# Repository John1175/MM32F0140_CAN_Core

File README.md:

# MM32F0140_CAN_Core
带CAN的MM32F0140核心板

KiCad绘制

CAN接口

SWD接口

USB串口

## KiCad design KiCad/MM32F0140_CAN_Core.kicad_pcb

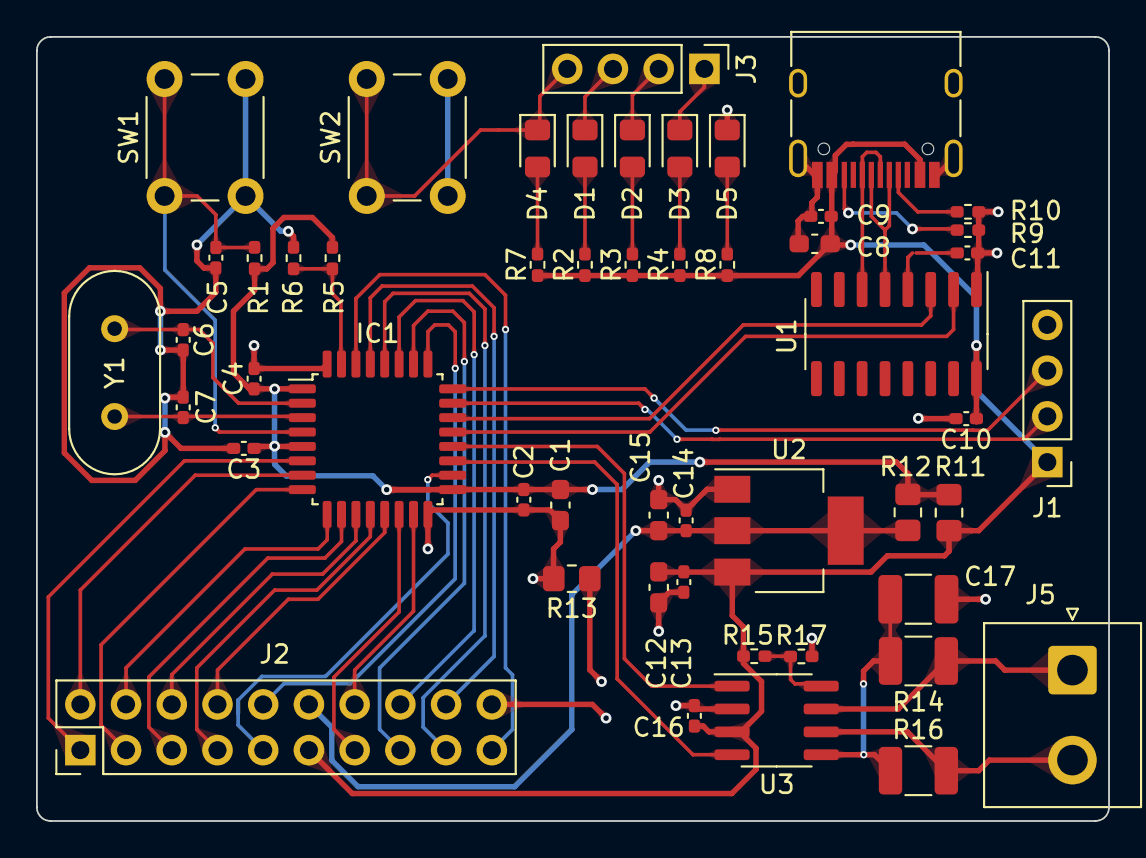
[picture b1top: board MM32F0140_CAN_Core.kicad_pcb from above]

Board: 2 copper layers, 59.6 x 43.6 mm, 51 parts (0 on the bottom side), 50 nets.

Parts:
C1, C8, C12, C15: 10uF; C_0603_1608Metric_Pad1.08x0.95mm_HandSolder
C2, C3, C4, C5, C9, C11, C13, C14, C16: 0.1uF; C_0402_1005Metric_Pad0.74x0.62mm_HandSolder
C6, C7: 22pF; C_0402_1005Metric_Pad0.74x0.62mm_HandSolder
C10: 0.47uF; C_0402_1005Metric_Pad0.74x0.62mm_HandSolder
C17: 4.7nF; C_1210_3225Metric_Pad1.33x2.70mm_HandSolder
D1, D2, D3, D4, D5: LED; LED_0805_2012Metric_Pad1.15x1.40mm_HandSolder
IC1: MM32F0144C4P; LQFP-32_7x7mm_P0.8mm
J1, J3: Conn_01x04; PinHeader_1x04_P2.54mm_Vertical
J2: Conn_02x10_Top_Bottom; PinHeader_2x10_P2.54mm_Vertical
J4: USB_C_Receptacle_USB2.0; USB_C_Receptacle_HRO_TYPE-C-31-M-12
J5: Conn_01x02; JST_NV_B02P-NV_1x02_P5.00mm_Vertical
R1: 100K; R_0402_1005Metric_Pad0.72x0.64mm_HandSolder
R2, R3, R4, R5, R6, R7, R8, R15, R17: 10K; R_0402_1005Metric_Pad0.72x0.64mm_HandSolder
R9, R10: 5.1K; R_0402_1005Metric_Pad0.72x0.64mm_HandSolder
R11, R12, R13: 0R; R_0805_2012Metric_Pad1.20x1.40mm_HandSolder
R14, R16: 60R; R_1210_3225Metric_Pad1.30x2.65mm_HandSolder
SW1, SW2: SW_Push; SW_PUSH_6mm_H5mm
U1: CH340C; SOIC-16_3.9x9.9mm_P1.27mm
U2: AMS1117; SOT-223-3_TabPin2
U3: TJA1040T; SOIC-8_3.9x4.9mm_P1.27mm
Y1: 8MHz; Crystal_HC49-U_Vertical

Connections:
+5V: C8.1, C9.1, C10.1, C12.1, C13.1, C16.1, J1.1, J2.11, J4.A4 (VBUS), J4.A9 (VBUS), J4.B4 (VBUS), J4.B9 (VBUS), R2.1, R3.1, R4.1, R7.1, R8.1, R11.1, R15.1, U1.16 (VCC), U2.3 (VI), U3.3 (VCC)
/CAN/CAN_RX: IC1.19 (PA9), U3.4 (RXD)
/CAN/CAN_TX: IC1.20 (PA10), U3.1 (TXD)
/Core/BOOT0: IC1.31 (PD5-BOOT0), R5.2, R6.1
/Core/NRST: C5.1, IC1.4 (NRST1), R1.2, SW1.1
/Core/OSC_I: C6.1, IC1.2 (PD0-OSC_IN), Y1.1
/Core/OSC_O: C7.1, IC1.3 (PD1-OSC_OUT), Y1.2
/Core/PA0: IC1.6 (PA0-WKUP), J2.1
/Core/PA1: IC1.7 (PA1), J2.2
/Core/PA2: IC1.8 (PA2), J2.3
/Core/PA3: IC1.9 (PA3), J2.4
/Core/PA4: IC1.10 (PA4), J2.5
/Core/PA5: IC1.11 (PA5), J2.6
/Core/PA6: IC1.12 (PA6), J2.7
/Core/PA7: IC1.13 (PA7), J2.8
/Core/PA8: IC1.18 (PA8), J2.9
/Core/PA15: IC1.25 (PA15), J2.10
/Core/PB0: IC1.14 (PB0), J2.13
/Core/PB1: IC1.15 (PB1), J2.14
/Core/PB3: IC1.26 (PB3), J2.15
/Core/PB4: IC1.27 (PB4), J2.16
/Core/PB5: IC1.28 (PB5), J2.17
/Core/PB6: IC1.29 (PB6), J2.18
/Core/PB7: IC1.30 (PB7), J2.19
/Core/SWCLK: IC1.24 (PA14), J1.3
/Core/SWDIO: IC1.23 (PA13), J1.2
/Core/UART3_RX: IC1.22 (PA12), U1.3 (RXD)
/Core/UART3_TX: IC1.21 (PA11), U1.2 (TXD)
/USB/D+: J4.A6 (D+), J4.B6 (D+), U1.6 (UD-)
/USB/D-: J4.A7 (D-), J4.B7 (D-), U1.5 (UD+)
GND: C8.2, C9.2, C10.2, C11.2, C12.2, C13.2, C14.2, C15.2, C16.2, C17.2, D5.1 (K), J1.4, J2.20, J4.A1 (GND), J4.A12 (GND), J4.B1 (GND), J4.B12 (GND), J4.S1 (SHIELD), R9.2, R10.2, R13.1, R17.2, SW2.2, U1.1 (GND), U2.1 (ADJ), U3.2 (GND)
unnamed: D1.2 (A), R2.2
unnamed: D1.1 (K), J3.3
unnamed: D2.2 (A), R3.2
unnamed: D2.1 (K), J3.2
unnamed: D3.2 (A), R4.2
unnamed: D3.1 (K), J3.1
unnamed: D4.2 (A), R7.2
unnamed: D4.1 (K), J3.4, SW2.1
unnamed: D5.2 (A), R8.2
unnamed: J4.A5 (CC1), R10.1
unnamed: J4.B5 (CC2), R9.1
unnamed: J5.1, R14.1, U3.7 (CANH)
unnamed: J5.2, R16.2, U3.6 (CANL)
unnamed: C11.1, U1.4 (V3)
unnamed: C17.1, R14.2, R16.1, U3.5 (SPLIT)
unnamed: R15.2, R17.1, U3.8 (STB)
VCC: C14.1, C15.1, J2.12, R12.1, U2.2 (VO)
VDD: C1.1, C2.1, C3.1, C4.1, IC1.1 (VDD_1), IC1.5 (VDDA), IC1.17 (VDD_2), R1.1, R5.1, R11.2, R12.2
VSS: C1.2, C2.2, C3.2, C4.2, C5.2, C6.2, C7.2, IC1.16 (VSS_1), IC1.32 (VSS_2), R6.2, R13.2, SW1.2

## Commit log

2023-04-06 Datasheet
2023-04-06 KiCad文件创建
2023-04-06 KiCad文件创建
    KiCad文件生成
2023-04-06 更新README
2023-04-07 更新原理图 23.4.7
    更新原理图 23.4.7
2023-04-07 更新原理图
    23.4.7
2023-04-07 更新原理图
    2023.4.7 23:34
2023-04-08 原理图完成
    2023.4.8:8:30
2023-04-08 更新封装
2023-04-09 昨日修改
2023-04-15 更新原理图，添加BOM
2023-04-15 PCB更新
2023-04-19 PCB初稿
2023-04-24 PCB基本完成
2023-04-25 PCB初稿与Gerber
